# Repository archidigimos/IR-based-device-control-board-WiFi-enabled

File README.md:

# IR-based-device-control-board-WiFi-enabled
Module used to control any sort of IR based device. The hardware is WiFi enabled which is used to receive the IR codes for the operation directly from the Server.
")

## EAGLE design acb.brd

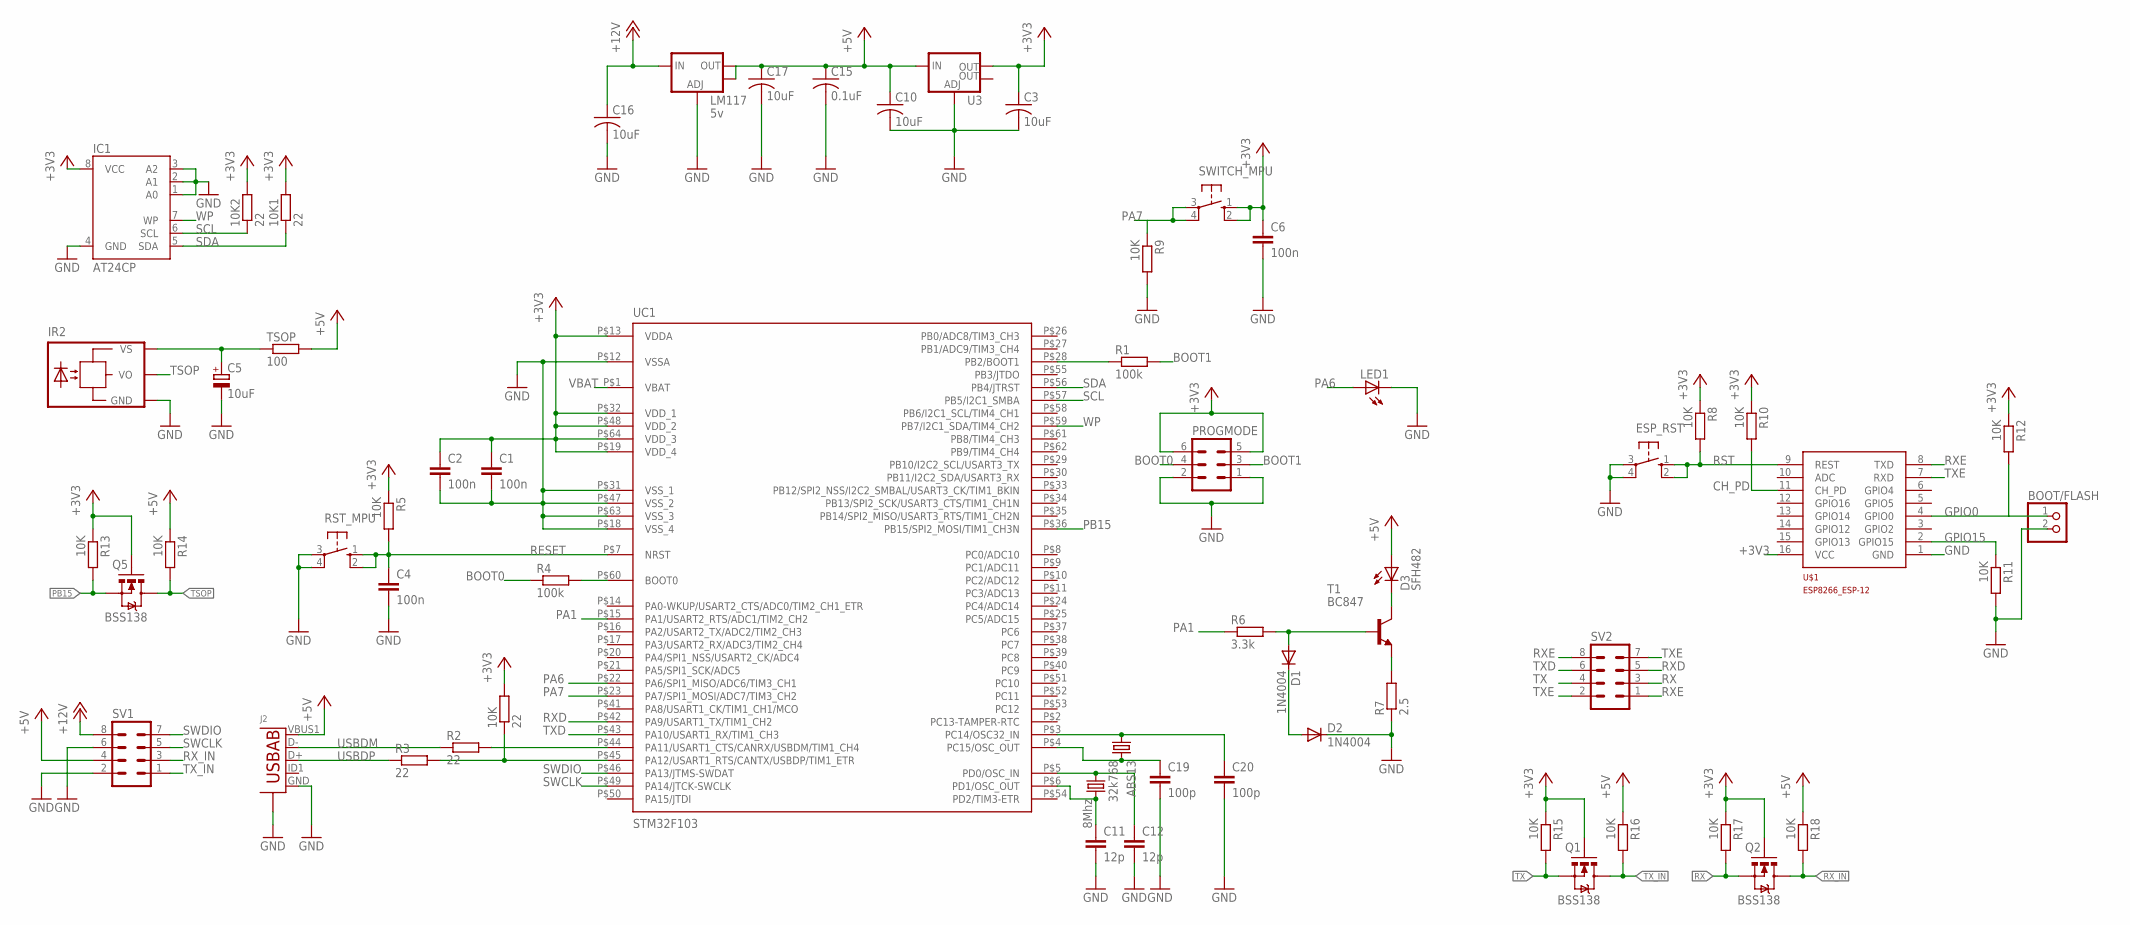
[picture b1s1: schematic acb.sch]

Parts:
10K, 10K1, 10K2: 22; R1206
ABS13: 32k768; 9HT7
BOOT/FLASH: PINHD-1X2; 1X02
C1, C2, C4, C6: 100n; C1206
C3, C10: 10uF; C1206
C5: 10uF; E2,5-6
C11, C12: 12p; C1206
C15: 0.1uF; C0805
C16, C17: 10uF; C0805
C19, C20: 100p; C1206
D1, D2: 1N4004; DO41-10
D3: SFH482
ESP_RST: 10-XX; B3F-10XX
IC1: AT24CP; DIL08
IR2: TSOP1730TB1; TSOP17_TB1
J2: USB-ABBG; USB-AB-MICRO-SMD_V03_SF
LED1: LED5MM
LM117: 5v; SOT223
PROGMODE: MA03-2
Q1, Q2, Q5: BSS138; SOT23-3
Q3: 8Mhz; HC49U-V
R1, R4: 100k; R1206
R2, R3: 22; R1206
R5, R8, R9, R10, R11, R12, R13, R14, R15, R16, R17, R18: 10K; R1206
R6: 3.3k; R1206
R7: 2.5; R1206
RST_MPU: 10-XX; B3F-10XX
SV1, SV2: MA04-2
SWITCH_MPU: 10-XX; B3F-10XX
T1: BC847; SOT23
TSOP: 100; R1206
U3: V_REG_LM1117SOT223; SOT223
U$1: ESP8266_ESP-12; ESP8266-ESP12
UC1: STM32F103; TQFP-10X10-64

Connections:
+3V3: 10K.2, 10K1.2, 10K2.2, C1.1, C2.1, C3.1, C6.1, IC1.8 (VCC), PROGMODE.5, PROGMODE.6, Q1.1 (G), Q2.1 (G), Q5.1 (G), R5.1, R8.1, R10.1, R12.1, R13.1, R15.1, R17.1, SWITCH_MPU.1 (S), SWITCH_MPU.2 (S1), U3.2 (OUT), U$1.16 (VCC), UC1.P$13 (VDDA), UC1.P$19 (VDD_4), UC1.P$32 (VDD_1), UC1.P$48 (VDD_2), UC1.P$64 (VDD_3)
+5V: C10.1, C15.1, C17.1, D3.A, J2.VBUS1 (VBUS), LM117.2 (OUT), LM117.4 (OUT), R14.1, R16.1, R18.1, SV1.4, TSOP.2, U3.3 (IN)
+12V: C16.1, LM117.3 (IN), SV1.8
BOOT0: PROGMODE.4, R4.1
BOOT1: PROGMODE.3, R1.2
CH_PD: R10.2, U$1.11 (CH_PD)
GND: BOOT/FLASH.2, C1.2, C2.2, C3.2, C4.2, C5.-, C6.2, C10.2, C11.2, C12.2, C15.2, C16.2, C17.2, C19.2, C20.2, D2.C, ESP_RST.3, ESP_RST.4 (P1), IC1.1 (A0), IC1.2 (A1), IC1.3 (A2), IC1.4 (GND), IR2.GND, J2.GND, J2.S1 (S), J2.S2 (S), J2.S3 (S), J2.S4 (S), LED1.K (C), LM117.1 (ADJ), PROGMODE.1, PROGMODE.2, R7.1, R9.2, R11.2, RST_MPU.3, RST_MPU.4 (P1), SV1.2, SV1.6, U3.1 (ADJ), U$1.1 (GND), UC1.P$12 (VSSA), UC1.P$18 (VSS_4), UC1.P$31 (VSS_1), UC1.P$47 (VSS_2), UC1.P$63 (VSS_3)
GPIO0: BOOT/FLASH.1, R12.2, U$1.4 (GPIO0)
GPIO15: R11.1, U$1.2 (GPIO15)
unnamed: R1.1, UC1.P$28 (PB2/BOOT1)
unnamed: R2.2, UC1.P$44 (PA11/USART1_CTS/CANRX/USBDM/TIM1_CH4)
unnamed: 10K.1, R3.2, UC1.P$45 (PA12/USART1_RTS/CANTX/USBDP/TIM1_ETR)
unnamed: R4.2, UC1.P$60 (BOOT0)
unnamed: C12.1, Q3.1, UC1.P$5 (PD0/OSC_IN)
unnamed: C11.1, Q3.2, UC1.P$6 (PD1/OSC_OUT)
unnamed: ABS13.4 (2), C19.1, UC1.P$4 (PC15/OSC_OUT)
unnamed: ABS13.1, C20.1, UC1.P$3 (PC14/OSC32_IN)
unnamed: C5.+, IR2.VS, TSOP.1
unnamed: D1.A, R6.2, T1.1 (B)
unnamed: D1.C, D2.A
unnamed: R7.2, T1.2 (E)
unnamed: D3.K (C), T1.3 (C)
PA1: R6.1, UC1.P$15 (PA1/USART2_RTS/ADC1/TIM2_CH2)
PA6: LED1.A, UC1.P$22 (PA6/SPI1_MISO/ADC6/TIM3_CH1)
PA7: R9.1, SWITCH_MPU.3, SWITCH_MPU.4 (P1), UC1.P$23 (PA7/SPI1_MOSI/ADC7/TIM3_CH2)
PB15: Q5.2 (S), R13.2, UC1.P$36 (PB15/SPI2_MOSI/TIM1_CH3N)
RESET: C4.1, R5.2, RST_MPU.1 (S), RST_MPU.2 (S1), UC1.P$7 (NRST)
RST: ESP_RST.1 (S), ESP_RST.2 (S1), R8.2, U$1.9 (REST)
RX: Q2.2 (S), R17.2, SV2.3
RXD: SV2.5, UC1.P$42 (PA9/USART1_TX/TIM1_CH2)
RXE: SV2.1, SV2.8, U$1.8 (TXD)
RX_IN: Q2.3 (D), R18.2, SV1.3
SCL: 10K2.1, IC1.6 (SCL), UC1.P$57 (PB5/I2C1_SMBA)
SDA: 10K1.1, IC1.5 (SDA), UC1.P$56 (PB4/JTRST)
SWCLK: SV1.5, UC1.P$49 (PA14/JTCK-SWCLK)
SWDIO: SV1.7, UC1.P$46 (PA13/JTMS-SWDAT)
TSOP: IR2.VO, Q5.3 (D), R14.2
TX: Q1.2 (S), R15.2, SV2.4
TXD: SV2.6, UC1.P$43 (PA10/USART1_RX/TIM1_CH3)
TXE: SV2.2, SV2.7, U$1.7 (RXD)
TX_IN: Q1.3 (D), R16.2, SV1.1
USBDM: J2.D-, R2.1
USBDP: J2.D+, R3.1
VBAT: UC1.P$1 (VBAT)
WP: IC1.7 (WP), UC1.P$59 (PB7/I2C1_SDA/TIM4_CH2)

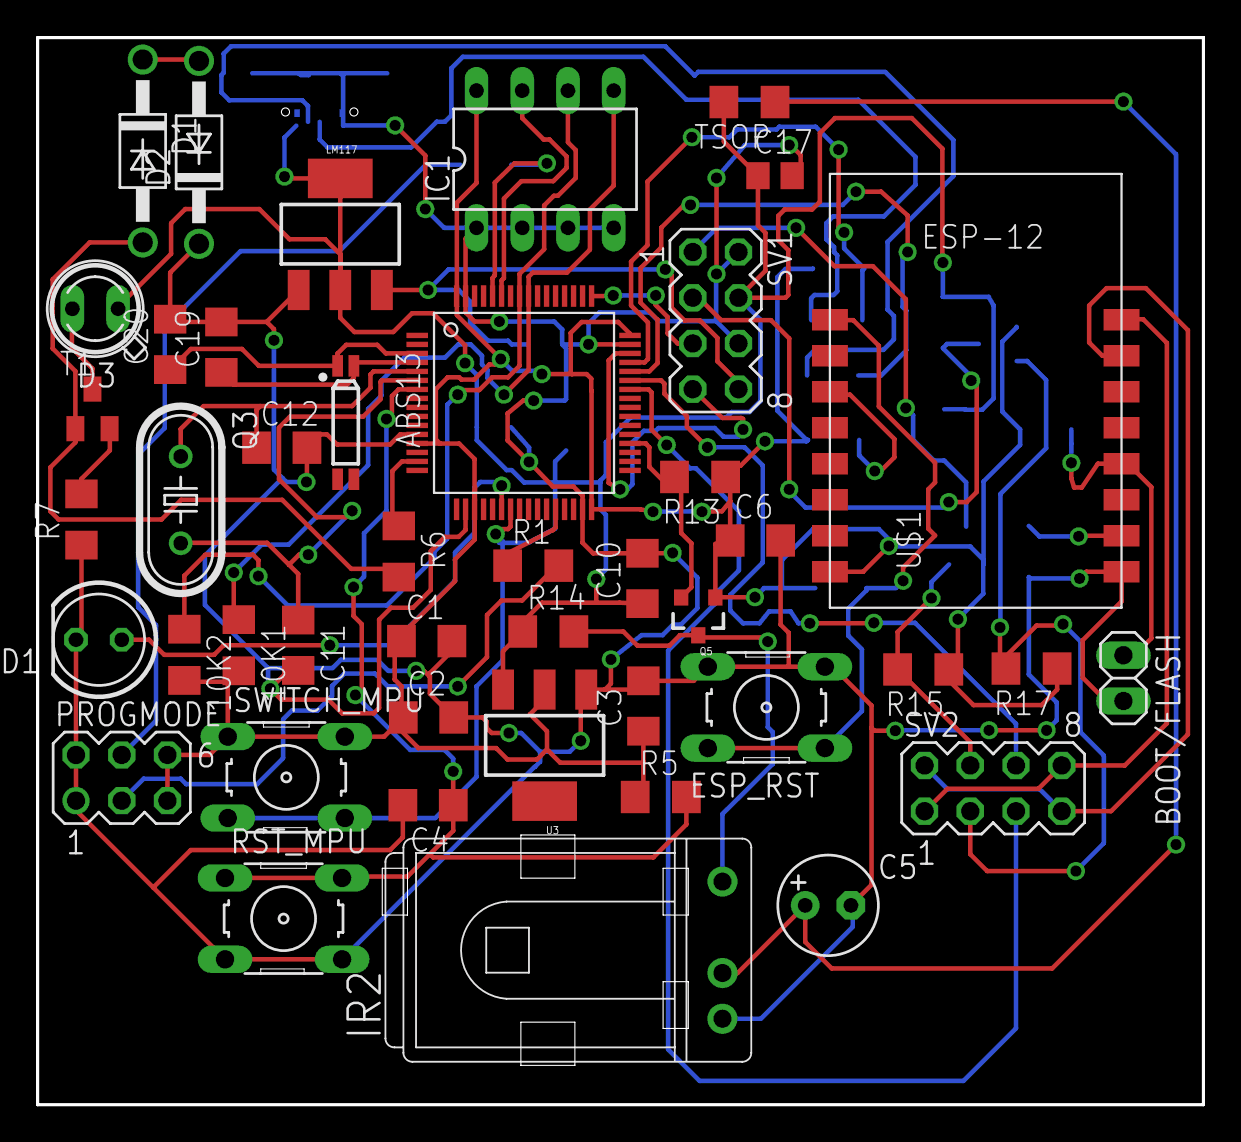
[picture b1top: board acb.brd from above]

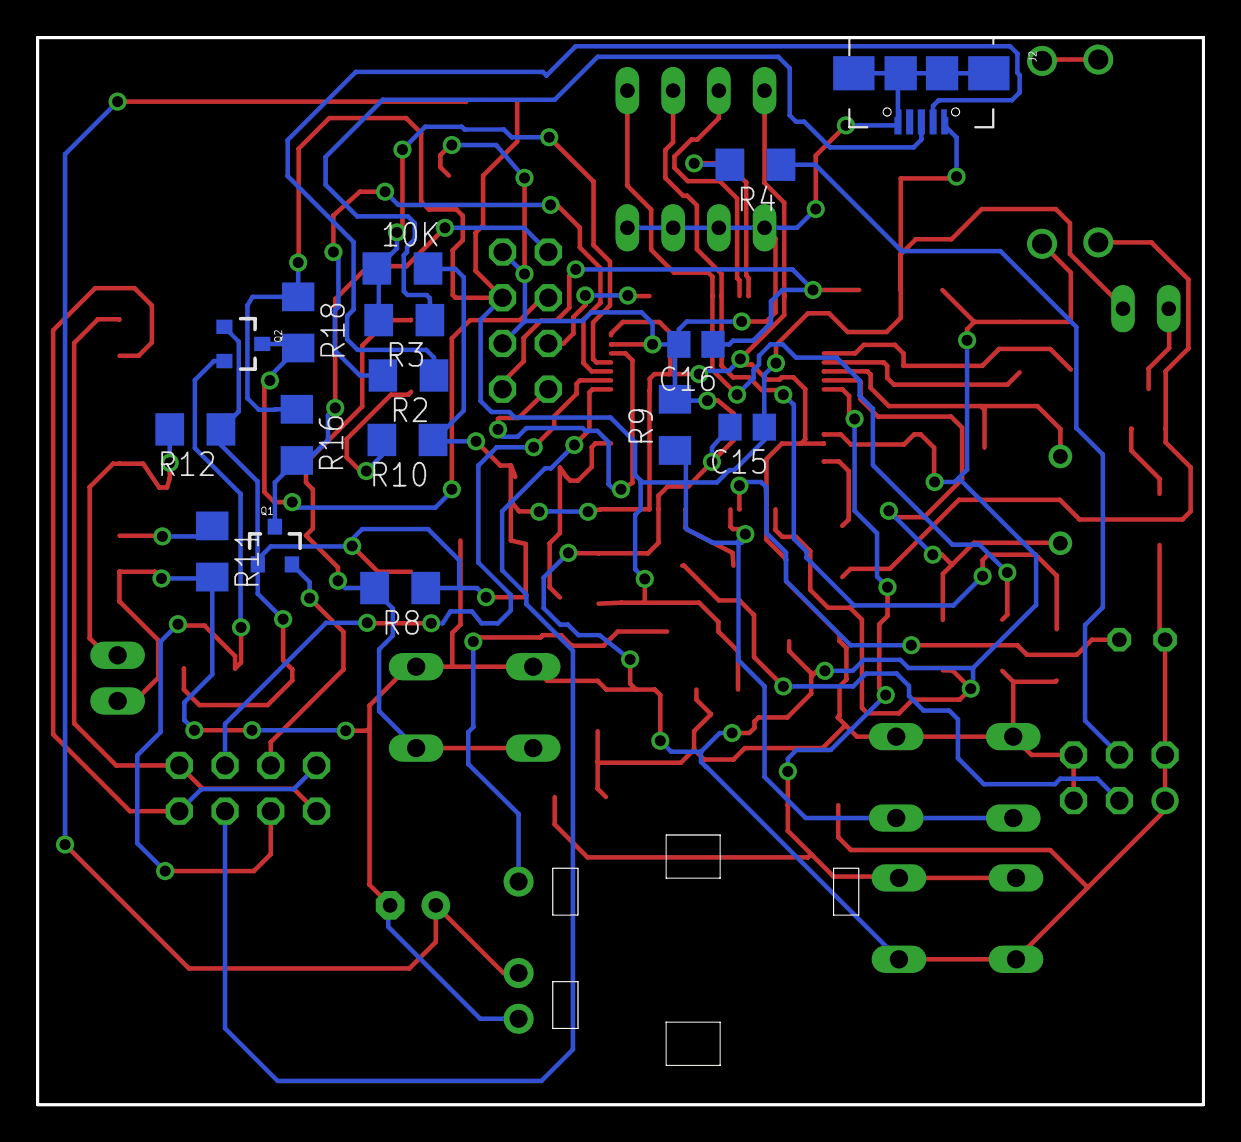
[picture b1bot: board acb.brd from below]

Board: 4 copper layers, 64.8 x 59.3 mm, 60 parts (16 on the bottom side), 44 nets.

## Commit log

2017-08-08 :tada: Added .gitattributes & .gitignore files
2017-08-08 Screenshot

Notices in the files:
parts and their libraries:
SparkFun-PowerIC: Licensing: Creative Commons ShareAlike 4.0 International - https://creativecommons.org/licenses/by-sa/4.0
